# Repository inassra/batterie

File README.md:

# Rachidi Inass, Cottar Manon

# Projet Batterie
# Sommaire 
### Introdcution
### I) L'alimentation
##### A) Cahier des charges
##### B) Piles et batterie 
### II) Développement du PCB
##### A) Régulateur Buck
##### B) Régulateur linéaire
##### C)Points Tests
### III) Les résultats
##### A) PCB de l’alimentation
##### B) Résultat du 6V
##### C) Résultat du 12V
### IV) Remarques 
##### A) Les chiffres
##### B) Nos erreurs
### Conclusion

### Introduction

Dans ce premier projet d'école d'ingénieur, il nous a été demandé de créer trois alimentations pour trois projets d'électronique différents.
Notre but, était donc de créer et réaliser un PCB opérationnel qui alimentera en tension et courant les composants utiles à la conception de ces projets.
Pour se faire, nous allons travailler sur un logiciel : Eagle 

### I) L'alimentation
##### A) Cahier des charges 

Il est nécessaire d'éditer un cahier des charges avant chaque début de projet. En effet, chacun d'eux est constitué de différents composants qui ont tous des caractéristiques d'alimentation, et de courant délivré qui leur sont propre. 

Nous avons donc répertorié tous les composants suivant leur datasheet

- Lorawan      5V 
               111 mA (transmission)
               2,1 µA (veille)
               6,7mA (Réception)

- STM32        3,3V
               50mA

- GPS          3,3v
               <25mA

- Accéléromètre 3,3V
                3,9mA

- Capteur humidité 5V
                   <1,5mA

- Capteur PH          5V

- Capteur température 3,3V
                      <100mA
 
 Il a également fallu déterminer l'autonomie que devait avoir l'alimentation pour chaque projet. 
 - 8h pour le travailleur isolé
 - 10h pour le badge Alzeihmer
 - 15h pour le composte

C'est avec ces renseignements que nous avons pu choisir les piles ou batteries utiles et adéquates.

##### B) Piles et batterie

L'avantage de notre projet actuel est que l'on a utilisé des piles non rechargeables qui nous délivraient les 6V voulus, tandis que les piles rechargeables, elles ne peuvent délivrer que 1,2V chacune ce qui ne fera pas exactement 6V en tension d'entrée. Cependant, qui dit piles non rechargeables dis moins d'autonomie; ce qui ne coincidera pas avec les attentes de l'acheteur si l'on commercialise le projet.

12V pour plus d'autonomie(contrainte de poids)

NB:Il est possible d'utiliser des piles rechargeables qui pourront delivrer du 4,8V (4 * 1,2V vu qu'on utilise un boitier pour 4 piles) mais dans ce cas on est obligé d'utiliser un régulateur BOOST afin de faire augmenter la tension jusqu'à 5V. Cette decision est possible mais pourra causer d'autres contraintes surtout que ce type de régulateur nécessite plus de composants ce qui veut dire que la partie alimentation va couter plus cher et va prendre plus d'espace ce qui n'est pas souhaiter pour le travailleur isolé ainsi que le badge alzheimer.
### II) Développement du PCB
##### A) Régulateur Buck
##### Pourquoi ? 

Comme vu dans le cahier des charges, nous avons plusieurs composants à alimenter. Les deux tensions à délivrer sont le 5V et le 3,3V. 
Pour cela, nous avions deux choix de régulateurs; soit un Buck (tension de sortie, du régulateur, abaissée) ou un régulateur Boost (le contraire; tension de sortie du régulateur augmentée, il inverse la tension). 

Sachant que, pour le composte, la batterie délivre 12V, le choix du régulateur Buck était alors une évidence. 
Nous avons, de plus, pris la décision de rester sur ce type de régulateur pour les deux autres projets.

Nous avons, donc, opté pour un MC34063A/E
Pourquoi ? 

- courant de sortie supérieur à 1,5mA, 
- large plage de tension d’entrée (3V-40V), sortie (0,8V-18V)
- Moins cher
- En stock
- capable du Boost et du Buck (option en plus)

 ##### L'environnement
 
Cependant, afin d’abaisser la tension, un simple régulateur dans un circuit électrique ne suffit pas. Il a besoin d’un environnement pour mener à bien sa mission. 
En effet, d’après la datasheet, de nombreux composants sont nécessaires.

En se référant à la datasheet du régulateur. 

Détaillons chacun d’eux : 

- Un résistance Rsc de 0,33 Ohm . Celle-ci permet de contrôler le courant maximal arrivant dans la pin Switch. 
- Un condensateur C2 (100µF) polarisé ; filtrage de parasites 
- Un condensateur C1(470µF) polarisé; filtrage de tension de sortie
- Une bobine ( 220µH); filtrage de courant de sortie. *
bobine en série et capa en parallèle = lissage 
- Une diode (40V) reliée à la masse, à la sortie de la switch. Elle agit comme une sécurité. En effet, si la tension dépasse 40V, alors tout passe par la diode et va à la masse. Cette valeur de tension peut paraître inatteignable de prime abord, car nous délivrons au maximum 12V en entrée, mais le On Off de la switch augmente la tension et peut atteindre ces 40V.
- Un condenstaur C3 (470pF) non polarisé; capa de synchronisation de charge et décharge du régulateur.
- 2 résistances R1 et R2. L'association de ces deux résistances forme un pont diviseur de tension, (pont diviseur de tension = abaisser une tension sans consommer de puissance).
A elles deux elles vont déterminer la tension de sortie du régulateur. En effet, lorsque l’on analyse “plus en profondeur” le régulateur en lui même, nous nous apercevons qu’il y un comparateur 1,25 tension de référence du régulateur. C’est cette comparaison qui va faire VOUT. 
On doit agir sur R1 et R2 pour VOUT. 

L’association de C2, C1 et la bobine permet au régulateur d’être le plus stable possible. 

(Chaque valeur des composants est déterminée suivant la datasheet).  

##### B) Régulateur linéaire
###### Pourquoi?
Tout comme le montre le cahier des charges du travailleur isolé, on a besoin d’alimenter la
carte STM32 ainsi que les deux capteurs GPS et Accéléromètre avec une tension de 3,3V.
Pour avoir cette tension de sortie, on pourra refaire le même régulateur BUCK pour passer
du 6V au 3,3V ou bien du 5V au 3,3V.
Pour des raisons de coût ainsi que d’optimisation d’espace sur le PCB, on a plutôt opté pour
un régulateur linéaire.

Contraintes:
Les limites d'utilisation du régulateur linéaire sont liées aux contraintes thermiques, car ce
dernier chauffe. Et il peut chauffer beaucoup ! La dissipation thermique du composant est
proportionnelle à la différence de tension qui règne entre son entrée et sa sortie, et du
courant qui le parcourt.
=> Donc est ce que celà peut nous causer un problème? Dans notre cas, pour éviter ce
soucis, on a relié le régulateur linéaire avec le BUCK pour avoir comme tension d’entrée de
ce régulateur un 5V au lieu de 6V. Ainsi, on minimise la différence de tension entre son
entrée et sa sortie. De plus, concernant le courant; le régulateur choisi ne fournit que 300mA
et on ne consomme 100mA maximum.
On choisit alors:

Ainsi grâce à ce choix: 
  -Le régulateur nous délivre une tension de sortie de 3,3V pour alimenter les différents composants.

  -Il nous délivre un courant de 300mA suffisant (sachant que la STM32 consomme du 50mA; l'accéléromètre du 3,9mA; et le GPS un courant inférieur à 25mA).

  -On a eu une livraison rapide vu que le composant était en stock.

  -On a optimisé de l’espace vu que ce régulateur ne nécessite pas beaucoup de composants contrairement au BUCK.

###### Alimentation:
En se référant sur la datasheet du NCV33375:

L’une des caractéristiques de ce régulateur est:

-Les deux condensateurs Cin et Cout servent à linéariser respectivement la tension d’entrée et de sortie.

-Si la pin ON/OFF reste flottante alors le régulateur ne marche pas, il est nécessaire de lui appliquer une tension. Pour éviter toute contrainte, on relie cette pin à Vin.  

##### C)Points Tests

Afin de vérifier le bon fonctionnement du module alimentation, nous avons créé des points tests sur le PCB. Ceux-ci vont permettre de tester les tensions de sortie de chaque régulateur. Ils apparaissent comme des débuggueurs de régulateurs. 
Pour se faire nous avons inséré une résistance nulle à la sortie du régulateur Buck. Celle-ci pouvant être soudée et dessoudée en fonction de ce que l’on souhaite faire. En effet, si elle est dessoudée, nous pouvons vérifier la tension de sortie du régulateur grâce à un multimètre. En la soudant, elle va permettre de lier les deux régulateurs entre eux. En fait, elle se comporte comme un lien entre les deux régulateurs. 

Nous avons également choisi de mettre 3 pins dans le PCB. Une pin Masse, une pin 3,3V et une pin 5V. Chaque pin étant reliée à la sortie du régulateur correspondant. 

Nous verrons plus tard, que lors de l'association sur le PCB de l'alimentation avec les autres modules (capteurs, lorawan...), la résistance nulle nous aura été bien utile pour vérifier le bon fonctionnement du régulateur Buck et ainsi résoudre quelques problèmes. 

Les composants trouvés, les datasheets analysées et les points tests ajoutés, nous avons pu réaliser notre PCB sous Eagle. 

### III) Résultats:
##### A) PCB de l’alimentation
Il nous a été conseillé de réalisé notre PCB avec résistances en 0603 car pas de consommation de puissance et économie de place.
Le PCB étant vérifié, nous avons pu lancer "la commande". Lorsque nous l'avons reçu, nous avons pu le souder en suivant le Board sous Eagle. 

En vert le régulateur BUCK
En orange le régulateur linéaire

Le PCB fini, nous avons pu passer à l'étape de vérification sous 6V et 12v de tension d'entrée. 
##### B) Les résultats en 6V et 12V

Pour vérifier ces tensions nous nous sommes servi d'un multimètre pointé sur les 3pins du connecteur. 

Nous avons bien les résultats attendus. Nous avons ensuite analysé ces résultats avec un oscilloscope. 

##### C) Les résultats à l'oscilloscope

Pour se faire, nous avons mis une sonde à la sortie du régulateur buck; soit l'entrée de la bobine; et une à la sortie de la bobine. 
Nous avons obtenu : 

Le signal jaune est la réponse en sortie du régulateur avant le lissage de la bobine.C'est la retranscription même de l'effet de la pin Switch (il y a un petit dépassement; certainement dû à l'usage des piles)
Le signal en violet est la réponse en sortie de la bobine. Nous voyons bien son effet sur le lissage du signal. 

De plus, nous remarquons bien que nous avons les 5V en sortie souhaités. ( les deux signaux se superposent); Notre PCB fonctionne.  

#### D) Les résultats du PCB de tout un projet

Notre PCB étant opérationnel, nous avons pu l'insérer dans celui du projet "Travailleur isolé".
Une fois commandé et soudé, nous avons vérifié que tout fonctionnait.

Grand désarois quand nous avons vu que ce n'était pas le cas... :)
En effet, les tensions de sorties n'étaient pas bonnes; 5V à la sortie du régulateur linéaire...

C'est à ce moment là que la résistance nulle nous a été bien utile.
En pouvant la dessouder, nous avons d'abord pu mesurer la tension de sortie du régulateur Buck indépendnat du reste du circuit. Cette tension était correcte. 
Puis, nous avons vérifié qu'il n'y avait pas de court-circuit et l'avons re-soudée pour établir le lien entre les deux régulateurs. 

Nous avons alors pris la tension de sortie du régulateur linéaire qui étonnement n'était pas à 3,3V mais à 5V. Après mainte recherches nous en avons conclu que le problème venait du microprocesseur qui avait brûlé le régulateur linéaire. 

### IV) Remarques
##### A) Les chiffres

Nous avons chiffré le coût de fabrication de l'alimentation. 

Ce qui revient la plus cher est donc les piles. Une solution pour y remédier ? 
Nous aurions pu utiliser un régulateur Boost avec moins de piles et des rechargeables. Cependant, le régulateur Boost a besoin de plus de composants que le Buck, ce qui ne coincide pas avec le fait de réduire le budget, et ne répondra pas à la contrainte d'espace imposée par le cahier des charges du travailleur isolé et du badge Alzeihmer.  
###### B) Nos erreurs : 

Dans cette partie de rapport nous avons répertorié les quelques erreurs et remarques que nous avons faites lors du projet. 

- Ne pas omettre le plan de masse sur Eagle
- Prêter attention à la largeur des pistes car la machine de l’Ensea ne peut en faire des trop petites. C’est pourquoi le premier PCB n’était pas exploitable. 
- Le via a proximité des pins SV1 n’était pas connecté au plan de masse; on a soudé un fil entre le via et celui-ci. 
- Ne pas confondre Masse et Terre 
- Ne pas confondre stabilité du régulateur Buck et linéarité du régulateur linéaire. 

NB : Avoir de bons yeux pour souder les résistances en 0603 :)

### Conclusion

A ce jour, notre projet d'alimentation est encore incomplet. En effet, indépendemment de tous les autres composants ou capteurs, elle fonctionne mais lorsqu'on l'insère dans un PCB complet, quelques problèmes surviennent.
Nous supposons que cela est dû aux autres composants qui consomment du courant, ou sont mal soudés. 
Il aurait été interessant d'avoir plus de temps pour chercher nos erreurs et ainsi faire fonctionner les différents projets. 

Par ailleurs,ce premier projet a été pour nous l'occasion de mettre à disposition nos différentes connaissances acquises et de travailler en groupe en échangeant et régroupant nos idées.

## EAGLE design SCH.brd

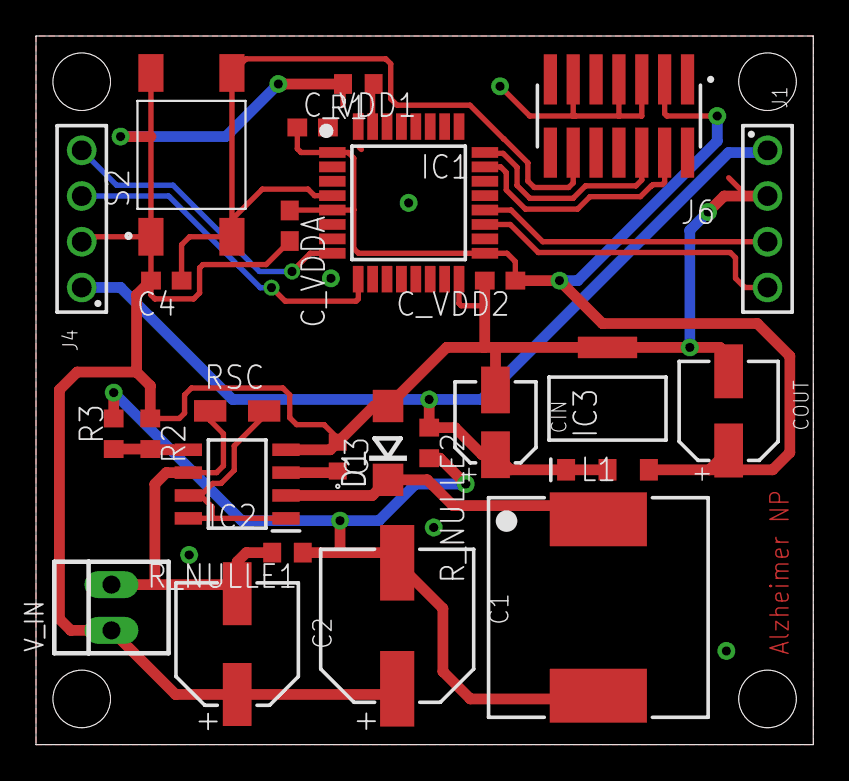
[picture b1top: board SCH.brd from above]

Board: 2 copper layers, 43.2 x 39.4 mm, 25 parts (0 on the bottom side), 17 nets.

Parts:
C1: 470 µF; WCAP-ASLL_8X10.5(DXL)
C2: 100 µF; WCAP-ASLL_6.3X7.7(DXL)
C3: C0603C471J5GACTU; C0603
C4: 0.1uF; C0603
CIN: 10 µF; WCAP-ASLL_4X5.5(DXL)
COUT: 22 µF; WCAP-ASLL_5X5.5(DXL)
C_VDD1, C_VDD2: 100nF; C0603
C_VDDA: 100nF; C0603
D1: DO214AC
IC1: STM32L412KBT6; QFP80P900X900X160-32N
IC2: MC34063ACD-TR; SOIC127P600X175-8N
IC3: NCV33375ST3.3T3G; SOT230P700X175-4N
J1, J4: 61300411121
J6: FTSH-107-01-L-DV; SAMTEC_FTSH-107-01-L-DV
L1: 220uH; WE-PDA_1260
R1: 100k; R0603
R2: 1.2K; R0603
R3: 3.6K; R0603
RSC: 0.33; R1206W
R_NULLE1, R_NULLE2: 0; R0603
S2: 2-1437565-7; SW_2-1437565-7
V_IN: 22-23-2021

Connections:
GND: C1.1, C2.1, C3.2, C4.2, CIN.2, COUT.2, C_VDD1.2, C_VDD2.2, C_VDDA.2, D1.A, IC1.16, IC1.32, IC2.4, IC3.4, J1.2, J4.2, J6.05, J6.07, J6.11, R1.2, R2.1, S2.1, S2.2, V_IN.1
unnamed: IC1.31, R1.1
unnamed: IC2.1, IC2.7, IC2.8, RSC.2
unnamed: IC2.5, R2.2, R3.1
unnamed: C3.1, IC2.3
unnamed: D1.C, IC2.2, L1.1
NRST: C4.1, IC1.4, J6.12, S2.3, S2.4
SWCLK: IC1.24, J6.06
SWDIO: IC1.23, J6.04
USART1_RX: IC1.20, J1.3
USART1_TX: IC1.19, J1.4
USART2_RX: IC1.9, J4.3
USART2_TX: IC1.8, J4.4
VCC_3V: COUT.1, C_VDD1.1, C_VDD2.1, C_VDDA.1, IC1.1, IC1.5, IC1.17, IC3.3, J6.03
VCC_5V: CIN.1, IC3.1, IC3.2, J1.1, J4.1, R_NULLE2.1
VCC_5V_IN: C1.2, L1.2, R3.2, R_NULLE1.1, R_NULLE2.2
VCC_6V: C2.2, IC2.6, RSC.1, R_NULLE1.2, V_IN.2

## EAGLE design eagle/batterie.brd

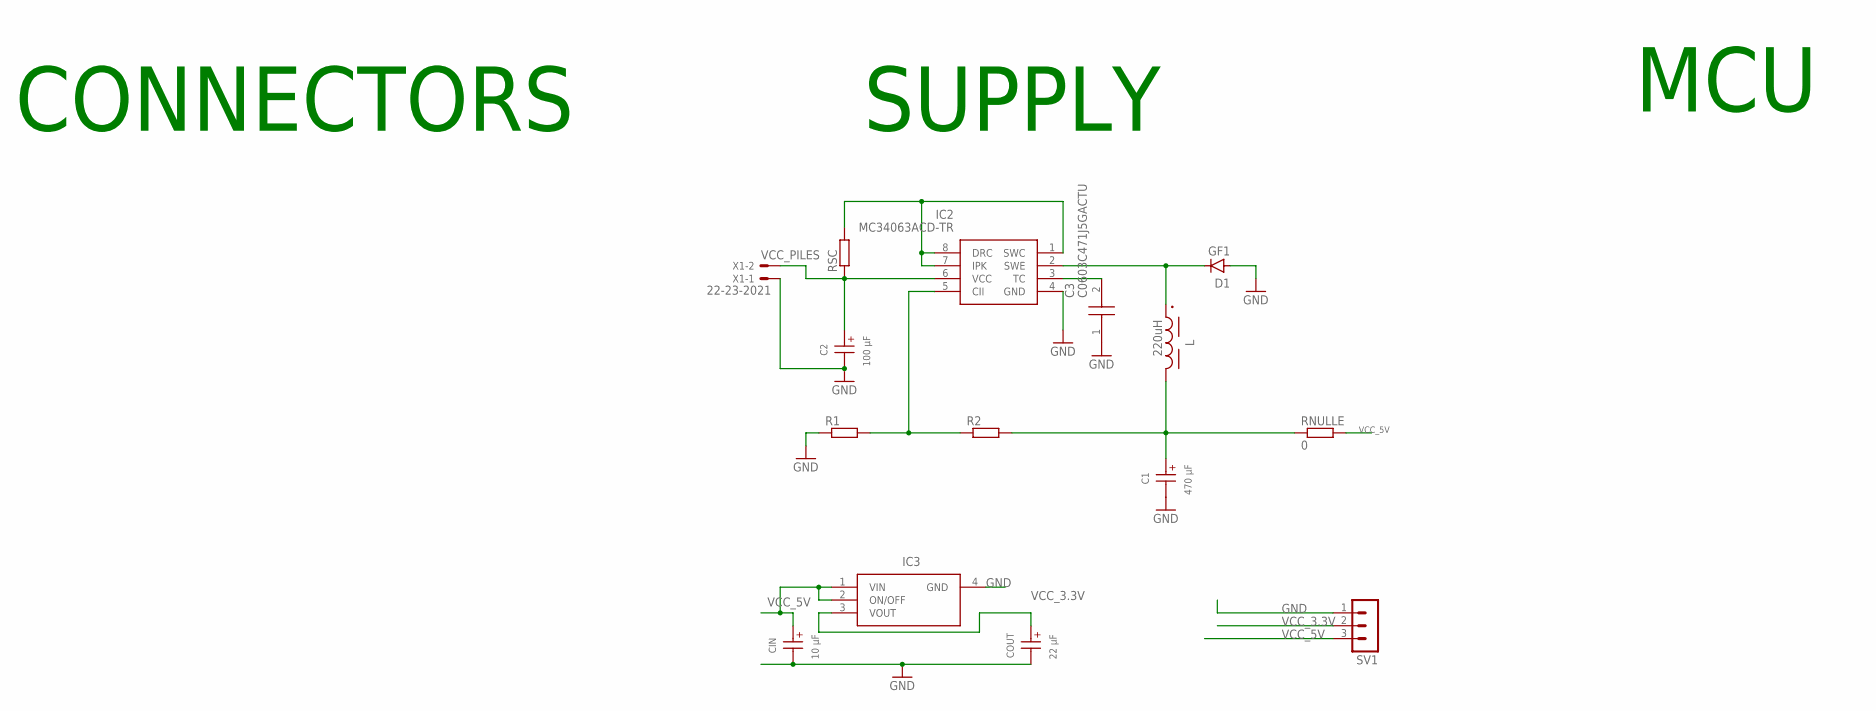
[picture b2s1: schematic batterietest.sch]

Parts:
C1: 470 µF; WCAP-ASLL_8X10.5(DXL)
C2: 100 µF; WCAP-ASLL_6.3X7.7(DXL)
C3: C0603C471J5GACTU; C0603
CIN: 10 µF; WCAP-ASLL_4X5.5(DXL)
COUT: 22 µF; WCAP-ASLL_5X5.5(DXL)
D1: GF1; SMA-DO214AC
IC2: MC34063ACD-TR; SOIC127P600X175-8N
IC3: NCV33375ST3.3T3G; SOT230P700X175-4N
L: 220uH; WE-PDA_1260
R1, R2: R-EU_R0603; R0603
RNULLE: 0; R0603
RSC: R-EU_R1206W; R1206W
SV1: MA03-1
X1: 22-23-2021

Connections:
GND: C1.2 (-), C2.2 (-), C3.1, CIN.2 (-), COUT.2 (-), D1.A, IC2.4 (GND), IC3.4 (GND), R1.1, SV1.1, X1.1
unnamed: C1.1 (+), L.2, R2.2, RNULLE.1
unnamed: IC2.1 (SWC), IC2.7 (IPK), IC2.8 (DRC), RSC.2
unnamed: IC2.5 (CII), R1.2, R2.1
unnamed: D1.K (C), IC2.2 (SWE), L.1
unnamed: C3.2, IC2.3 (TC)
VCC_3.3V: COUT.1 (+), IC3.3 (VOUT), SV1.2
VCC_5V: CIN.1 (+), IC3.1 (VIN), IC3.2 (ON/OFF), RNULLE.2, SV1.3
VCC_PILES: C2.1 (+), IC2.6 (VCC), RSC.1, X1.2

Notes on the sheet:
CONNECTORS
SUPPLY
MCU

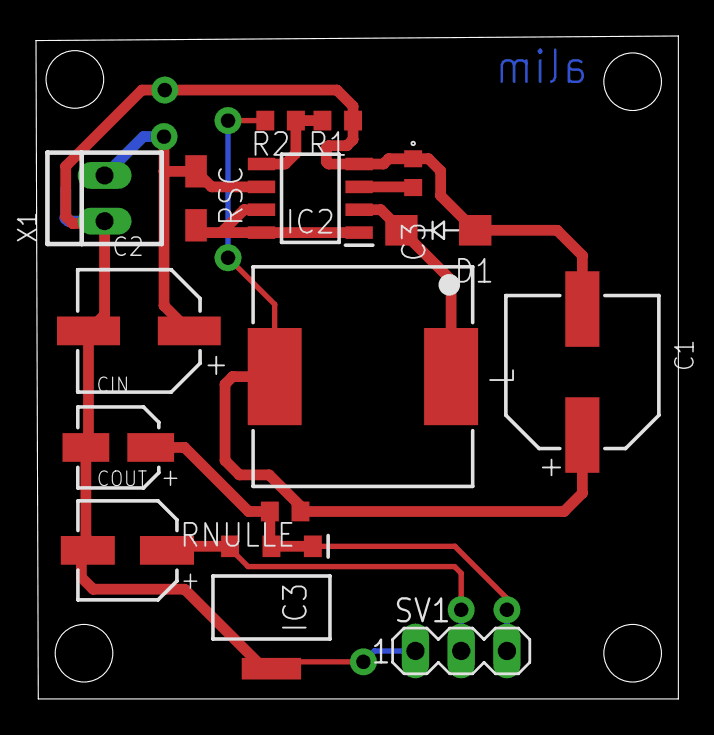
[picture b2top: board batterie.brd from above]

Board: 2 copper layers, 35.7 x 36.8 mm, 15 parts (0 on the bottom side), 9 nets.

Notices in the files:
parts and their libraries:
C1: Copyright: Würth Elektronik
